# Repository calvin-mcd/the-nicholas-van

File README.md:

# The Nicholas Van
 
The Nicholas Van is an EC (topre) pcb for trashman's [v4n4g0n](https://trashman.wiki/keyboards/v4n4g0n) keyboard. The pcb supports a both the 625U spacebar, and the split 275U, 225U spacebars. But each need their own respective plate. 
Some plate files can be found in the Production folder. Check the plate & hardware section beelow for what you will need. 
The pcb comes with a usb port by default, but supports a Daughterboard connector (either jst or pico). It also supports another 5pin Jst connector for the Rotary Encoder board from the Embrace.

***VERSIONS***:
In the production folder you will find both the prototype production files and the revision files (as well as various plate files). Please be aware of their differences and what aspects have not been confirmed to work yet when ordering pcbs.
- The prototype was sporting a STM32F401 MCU and its rgb could not be made to work. This could have been a firmware issue, but hardware issues could not be ruled out. Otherwise the pcb was fully working
- The revision is using a STM32F072 MCU and simplified components and an attempt to fix the rgb hardware. The revision has not been prototyped yet and firmware needs to be adapted to its rgb hardware setup.

## Layout

[Link](http://www.keyboard-layout-editor.com/#/gists/a55206434a137895f2c476b4f5ef8018)

## Images

## Firmware

The basic EC firmware is ready to go and the source code is provided for tweaking any settings.

## Plates & Hardware

Plate files are available for OEM (original and deskey housings), for each respective bottom row choice, and for the original plate, Hull and Embrace cases.

Furthermore, you will need 26x 10mm M2 screws and M2 nuts to assemble the pcb. O-rings might help aligning the pcb and usb port in some cases, but is not required.

## Disclaimer

Please note that this project is a work in progress with no guarantees of a working outcome. No-one involved in this project is responsible for any usage issues that may arise. Order at your own risk. Support will not be provided but pull requests will be reviewed and possibly accepted.

## License

Shield: 

This work is licensed under a  
[Creative Commons Attribution-NonCommercial-ShareAlike 4.0 International License](http://creativecommons.org/licenses/by-nc-sa/4.0/).

## Credits

big thanks to M4NU for repeatedly begging for a topre vanagon pcb! ;)

Otherwise, many thanks for feedback, help, references go to Sporkus, Cipulot\#8455 & matthewdias\#2671.

Any questions, contact Calvin0563 on Discord.

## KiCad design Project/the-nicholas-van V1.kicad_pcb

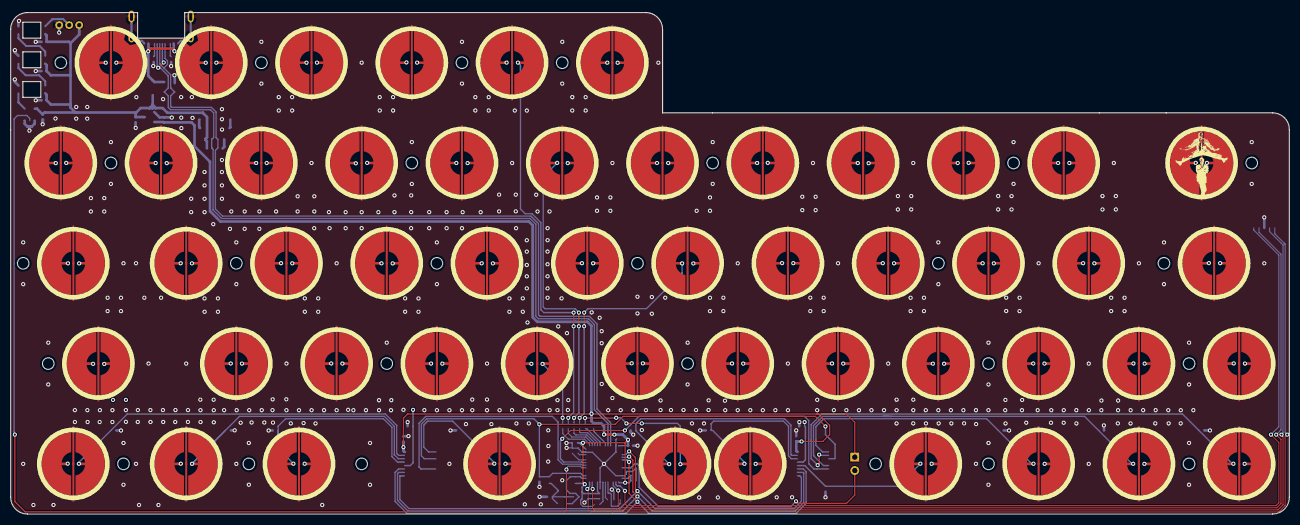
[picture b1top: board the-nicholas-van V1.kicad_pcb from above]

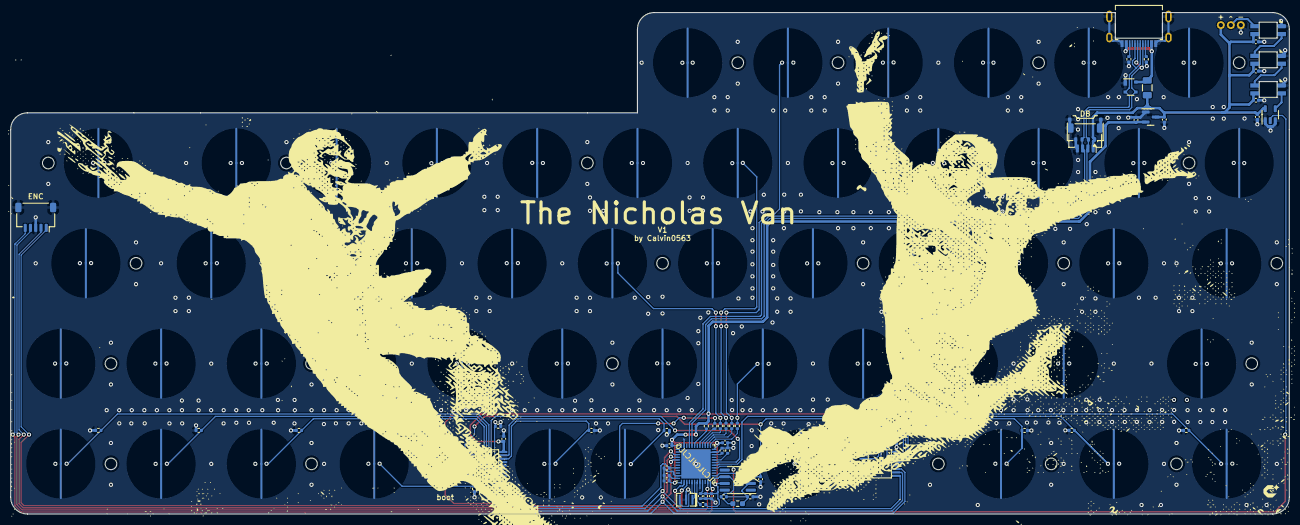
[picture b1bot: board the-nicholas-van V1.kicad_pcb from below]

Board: 4 copper layers, 242.9 x 95.2 mm, 139 parts (61 on the bottom side), 54 nets.

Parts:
C1: 4.7u; C_0402_1005Metric
C2, C3, C4, C5, C6, C11, C13, C14, C15, C16, C17, C18: 100n; C_0402_1005Metric
C7, C8, C9: 1u; C_0402_1005Metric
C12: 220p; C_0402_1005Metric
D1: PRTR5V0U2X; SOT-143
F_USBC1: 500mA; Fuse_1206_3216Metric
H1, H2, H3, H4, H5, H6, H7, H8, H9, H10, H11, H12, H13, H14, H15, H16, H17, H18, H19, H20, H21, H22, H23, H24, H25, H26: MountingHole; HOLE_M2
J1: JST SH; JST_SH_SM04B-SRSS-TB_1x04-1MP_P1.00mm_Horizontal
J2: Pico EZmate; Molex_Pico-EZmate_78171-0004_1x04-1MP_P1.20mm_Vertical
J3: USB_C sink board 1.3mm; USB4510031A
J4: Conn_01x05; JST_SH_SM05B-SRSS-TB_1x05-1MP_P1.00mm_Horizontal
J5: ARGB; PinHeader_1x03_P1.27mm_Vertical
JP1: Ext_Res; R_0603_1608Metric_Pad0.98x0.95mm_HandSolder
LED1, LED2, LED3: SK6812MINI-E; SK6812-MINI-E
R1, R7, R10, R15, R16, R17, R18, R20, R21, R22, R23, R24, R25, R26: 100k; R_0402_1005Metric
R2, R3, R4, R5, R6: 100; R_0402_1005Metric
R8, R9, R11: 10k; R_0402_1005Metric
R12, R13: 5.1k; R_0402_1005Metric
R19: 1k; R_0402_1005Metric
SW1: BOOT0; PinHeader_1x02_P2.54mm_Vertical
SW_EC1, SW_EC2, SW_EC3, SW_EC4, SW_EC5, SW_EC6, SW_EC7, SW_EC8, SW_EC9, SW_EC10, SW_EC11, SW_EC12, SW_EC13, SW_EC14, SW_EC15, SW_EC16, SW_EC17, SW_EC18, SW_EC19, SW_EC20, SW_EC21, SW_EC22, SW_EC23, SW_EC24, SW_EC25, SW_EC26, SW_EC27, SW_EC28, SW_EC29, SW_EC30, SW_EC31, SW_EC32, SW_EC33, SW_EC34, SW_EC35, SW_EC36, SW_EC37, SW_EC38, SW_EC39, SW_EC40, SW_EC41, SW_EC42, SW_EC43, SW_EC44, SW_EC45, SW_EC46, SW_EC47, SW_EC48, SW_EC49, SW_EC50, SW_EC51, SW_EC54: Topre; ecs_pad_1U_no_ring
U1: STM32F401CBUx; QFN-48-1EP_7x7mm_P0.5mm_EP5.6x5.6mm
U2: XC6206PxxxMR; SOT-23
U3: 74AHCT1G125; SOT-23-5
U4, U6: 74HC4051; TSSOP16
U5: OPA350; SOIC-8_3.9x4.9mm_P1.27mm
Y1: 8 MHz; Resonator_SMD_Murata_CSTxExxV-3Pin_3.0x1.1mm

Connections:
+5V: C8.1, C15.1, C16.1, C17.1, C18.1, F_USBC1.2, J1.1, J2.1, J5.3, LED1.1 (VDD), LED2.1 (VDD), LED3.1 (VDD), U2.3 (VI), U3.5 (+5V)
ADC: JP1.1 (A), R7.2, U1.13 (PA3), U5.6 (OUT)
AMUX_SEL_0: U1.41 (PB5), U4.11 (S0), U6.11 (S0)
AMUX_SEL_1: U1.40 (PB4), U4.10 (S1), U6.10 (S1)
AMUX_SEL_2: U1.39 (PB3), U4.9 (S2), U6.9 (S2)
APLEX_EN_PIN_0: U1.18 (PB0), U4.6 (~E)
APLEX_EN_PIN_1: U1.19 (PB1), U6.6 (~E)
APLEX_OUT_PIN_0: C12.2, U1.14 (PA4), U4.3 (A), U5.3 (IN+), U6.3 (A)
ARGB: J5.2, LED3.2 (DOUT)
ARGB_3V3: U1.17 (PA7), U3.2
ARGB_5V: LED1.4 (DIN), U3.4
BOOT0: R11.1, SW1.2 (B), U1.44 (BOOT0)
BOOT1: R9.2, U1.20 (PB2)
COL0: R16.1, SW_EC1.2, SW_EC7.2, SW_EC19.2, SW_EC31.2, SW_EC43.2, U4.15 (A2)
COL1: R15.1, SW_EC2.2, SW_EC8.2, SW_EC20.2, SW_EC32.2, SW_EC44.2, U4.14 (A1)
COL2: R10.1, SW_EC3.2, SW_EC9.2, SW_EC21.2, SW_EC33.2, SW_EC45.2, U4.13 (A0)
COL3: R17.1, SW_EC4.2, SW_EC10.2, SW_EC22.2, SW_EC34.2, U4.12 (A3)
COL4: R18.1, SW_EC5.2, SW_EC11.2, SW_EC23.2, SW_EC35.2, SW_EC46.2, U4.1 (A4)
COL5: R22.1, SW_EC6.2, SW_EC12.2, SW_EC24.2, SW_EC36.2, SW_EC47.2, U6.15 (A2)
COL6: R21.1, SW_EC13.2, SW_EC25.2, SW_EC37.2, SW_EC48.2, U6.14 (A1)
COL7: R20.1, SW_EC14.2, SW_EC26.2, SW_EC38.2, U6.13 (A0)
COL8: R23.1, SW_EC15.2, SW_EC27.2, SW_EC39.2, SW_EC49.2, U6.12 (A3)
COL9: R24.1, SW_EC16.2, SW_EC28.2, SW_EC40.2, SW_EC50.2, U6.1 (A4)
COL10: R25.1, SW_EC17.2, SW_EC29.2, SW_EC41.2, SW_EC51.2, U6.5 (A5)
COL11: R26.1, SW_EC18.2, SW_EC30.2, SW_EC42.2, SW_EC54.2, U6.2 (A6)
D+: D1.2 (I/O1), J1.3, J2.3, J3.A6 (D+), J3.B6 (D+), U1.33 (PA12)
D-: D1.3 (I/O2), J1.2, J2.2, J3.A7 (D-), J3.B7 (D-), U1.32 (PA11)
ENC1: J4.2, U1.3 (PC14)
ENC2: J4.4, U1.11 (PA1)
GND: C1.2, C2.2, C3.2, C4.2, C5.2, C6.2, C7.2, C8.2, C9.2, C11.2, C12.1, C13.2, C14.2, C15.2, C16.2, C17.2, C18.2, D1.1 (GND), J1.4, J1.MP (MountPin), J2.4, J2.MP (MountPin), J3.A1 (GND), J3.A12 (GND), J3.S1 (SHIELD), J4.3, J4.MP (MountPin), J5.1, LED1.3 (VSS), LED2.3 (VSS), LED3.3 (VSS), R9.1, R10.2, R11.2, R12.2, R13.2, R15.2, R16.2, R17.2, R18.2, R19.2, R20.2, R21.2, R22.2, R23.2, R24.2, R25.2, R26.2, SW_EC1.3, SW_EC2.3, SW_EC3.3, SW_EC4.3, SW_EC5.3, SW_EC6.3, SW_EC7.3, SW_EC8.3, SW_EC9.3, SW_EC10.3, SW_EC11.3, SW_EC12.3, SW_EC13.3, SW_EC14.3, SW_EC15.3, SW_EC16.3, SW_EC17.3, SW_EC18.3, SW_EC19.3, SW_EC20.3, SW_EC21.3, SW_EC22.3, SW_EC23.3, SW_EC24.3, SW_EC25.3, SW_EC26.3, SW_EC27.3, SW_EC28.3, SW_EC29.3, SW_EC30.3, SW_EC31.3, SW_EC32.3, SW_EC33.3, SW_EC34.3, SW_EC35.3, SW_EC36.3, SW_EC37.3, SW_EC38.3, SW_EC39.3, SW_EC40.3, SW_EC41.3, SW_EC42.3, SW_EC43.3, SW_EC44.3, SW_EC45.3, SW_EC46.3, SW_EC47.3, SW_EC48.3, SW_EC49.3, SW_EC50.3, SW_EC51.3, SW_EC54.3, U1.8 (VSSA), U1.23 (VSS), U1.35 (VSS), U1.47 (VSS), U1.49 (VSS), U2.1 (GND), U3.1, U3.3 (GND), U4.2 (A6), U4.4 (A7), U4.5 (A5), U4.7 (VEE), U4.8 (GND), U5.4 (V-), U6.4 (A7), U6.7 (VEE), U6.8 (GND), Y1.2
NRST: R8.2, U1.7 (NRST)
unnamed: J3.A5 (CC1), R12.1
unnamed: J3.B5 (CC2), R13.1
unnamed: JP1.2 (B), R7.1, R19.1, U5.2 (IN-)
unnamed: LED1.2 (DOUT), LED2.4 (DIN)
unnamed: LED2.2 (DOUT), LED3.4 (DIN)
unnamed: R6.2, U1.29 (PA8)
unnamed: R1.1, U1.31 (PA10)
unnamed: R2.2, U1.25 (PB12)
unnamed: R3.2, U1.26 (PB13)
unnamed: R4.2, U1.27 (PB14)
unnamed: R5.2, U1.28 (PB15)
unnamed: C1.1, U1.22 (VCAP1)
ROW0: R3.1, SW_EC1.1, SW_EC2.1, SW_EC3.1, SW_EC4.1, SW_EC5.1, SW_EC6.1
ROW1: R4.1, SW_EC7.1, SW_EC8.1, SW_EC9.1, SW_EC10.1, SW_EC11.1, SW_EC12.1, SW_EC13.1, SW_EC14.1, SW_EC15.1, SW_EC16.1, SW_EC17.1, SW_EC18.1
ROW2: R5.1, SW_EC19.1, SW_EC20.1, SW_EC21.1, SW_EC22.1, SW_EC23.1, SW_EC24.1, SW_EC25.1, SW_EC26.1, SW_EC27.1, SW_EC28.1, SW_EC29.1, SW_EC30.1
ROW3: R2.1, SW_EC31.1, SW_EC32.1, SW_EC33.1, SW_EC34.1, SW_EC35.1, SW_EC36.1, SW_EC37.1, SW_EC38.1, SW_EC39.1, SW_EC40.1, SW_EC41.1, SW_EC42.1
ROW4: R6.1, SW_EC43.1, SW_EC44.1, SW_EC45.1, SW_EC46.1, SW_EC47.1, SW_EC48.1, SW_EC49.1, SW_EC50.1, SW_EC51.1, SW_EC54.1
SW1: J4.1, U1.2 (PC13)
SW2: J4.5, U1.12 (PA2)
VBAT: C2.1, C3.1, C4.1, C5.1, C6.1, C7.1, C9.1, C11.1, C13.1, C14.1, R1.2, R8.1, SW1.1 (A), U1.1 (VBAT), U1.9 (VREF+), U1.24 (VDD), U1.36 (VDD), U1.48 (VDD), U2.2 (VO), U4.16 (VCC), U5.7 (V+), U6.16 (VCC)
VCC: D1.4 (VCC), F_USBC1.1, J3.A4 (VBUS), J3.A9 (VBUS)
XTAL0: U1.5 (PH0), Y1.3
XTAL1: U1.6 (PH1), Y1.1

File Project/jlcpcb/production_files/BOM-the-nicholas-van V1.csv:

Comment,Designator,Footprint,LCSC
1k,R19,R_0402_1005Metric,C11702
STM32F401CBUx,U1,QFN-48-1EP_7x7mm_P0.5mm_EP5.6x5.6mm,C118825
74AHCT1G125,U3,SOT-23-5,C12494
OPA350,U5,SOIC-8_3.9x4.9mm_P1.27mm,C13388
Conn_01x05,J4,JST_SH_SM05B-SRSS-TB_1x05-1MP_P1.00mm_Horizontal,C136657
220p,C12,C_0402_1005Metric,C1530
JST SH,J1,JST_SH_SM04B-SRSS-TB_1x04-1MP_P1.00mm_Horizontal,C160404
4.7u,C1,C_0402_1005Metric,C23733
100,"R2,R3,R4,R5,R6",R_0402_1005Metric,C25076
100k,"R1,R10,R15,R16,R17,R18,R20,R21,R22,R23,R24,R25,R26,R7",R_0402_1005Metric,C25741
10k,"R11,R8,R9",R_0402_1005Metric,C25744
5.1k,"R12,R13",R_0402_1005Metric,C25905
PRTR5V0U2X,D1,SOT-143,C2827688
USB_C sink board 1.3mm,J3,USB4510031A,C3019717
100n,"C11,C13,C14,C15,C16,C17,C18,C2,C3,C4,C5,C6",C_0402_1005Metric,C307331
SK6812MINI-E,"LED1,LED2,LED3",SK6812-MINI-E,C5149201
1u,"C7,C8,C9",C_0402_1005Metric,C52923
XC6206PxxxMR,U2,SOT-23,C5446
74HC4051,"U4,U6",TSSOP16,C5645
500mA,F_USBC1,Fuse_1206_3216Metric,C70076
8 MHz,Y1,Resonator_SMD_Murata_CSTxExxV-3Pin_3.0x1.1mm,C907975

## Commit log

2023-09-15 project initialised
2023-09-24 created production files
2023-10-01 fresh production files
2023-10-11 backup
2023-11-17 added rgb breakout
2023-12-02 rgb symbol/footprint mismatch corrected, fresh gerbers, etc
2024-01-31 changed rgb pin for better compatibilty
2024-02-23 MX support pcb and plate
2024-03-30 plate revisions
2024-08-05 revision V1
    changed bottom row mounting and boot cut for plates
2024-08-11 v1 work
2024-08-28 revision update
2024-11-26 update revision
2024-12-22 publishing changes
2025-03-01 update production files
    before release
2025-05-08 firmware added
